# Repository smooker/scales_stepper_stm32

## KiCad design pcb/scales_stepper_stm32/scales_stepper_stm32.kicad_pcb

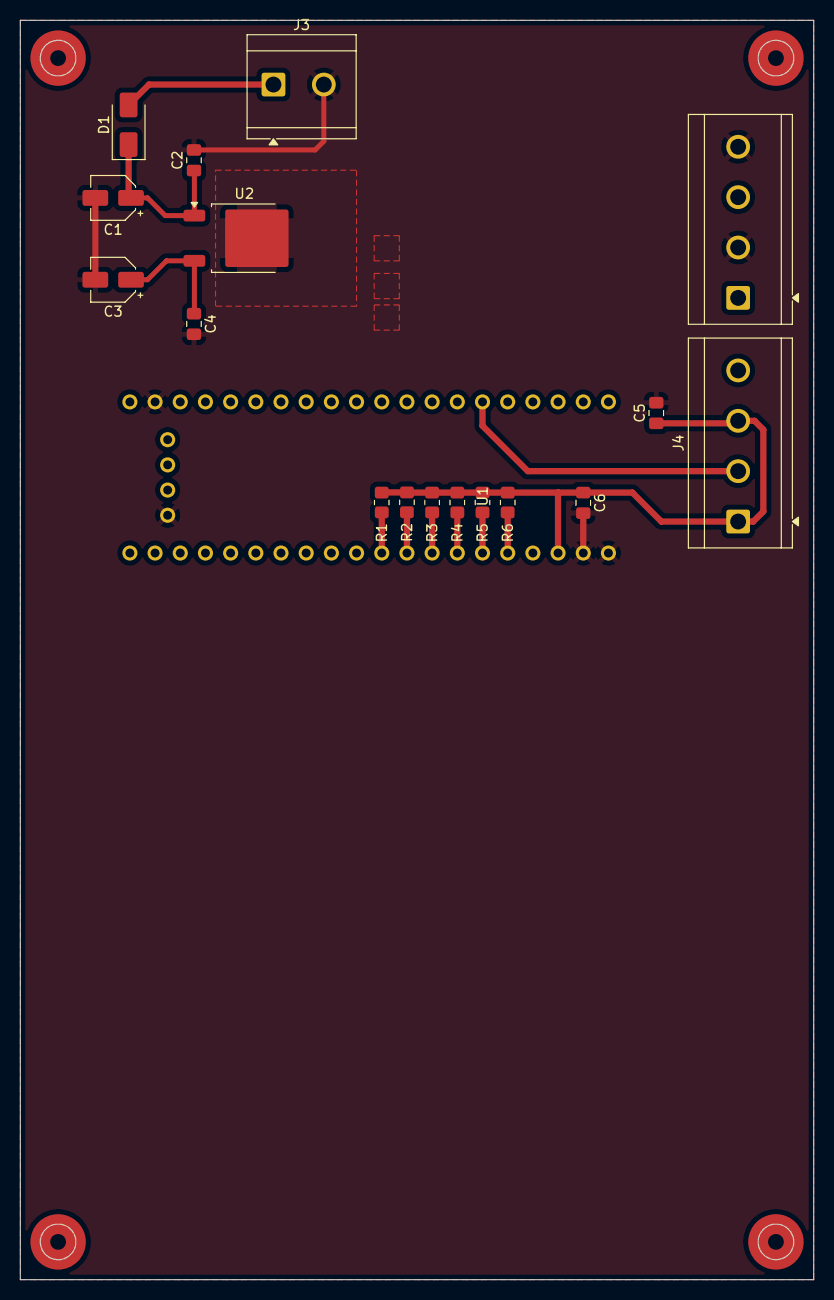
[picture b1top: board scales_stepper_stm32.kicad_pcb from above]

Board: 2 copper layers, 80.0 x 127.0 mm, 18 parts (0 on the bottom side), 13 nets.

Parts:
C1, C3: 47u; CP_Elec_4x4.5
C2, C4, C5, C6: 100n; C_0805_2012Metric_Pad1.18x1.45mm_HandSolder
D1: SS3200; D_SMA
J3: Screw_Terminal_01x02; TerminalBlock_CUI_TB007-508-02_1x02_P5.08mm_Horizontal
J4, J5: Screw_Terminal_01x04; TerminalBlock_CUI_TB007-508-04_1x04_P5.08mm_Horizontal
R1, R2, R3, R4, R5, R6: 1k; R_0805_2012Metric_Pad1.20x1.40mm_HandSolder
U1: BP; blue_pill
U2: LM78M05_TO252; TO-252-2

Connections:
+3V3: C5.1, C6.1, J4.1, J4.3, R1.1, R2.1, R3.1, R4.1, R5.1, R6.1, U1.3V3 (3.3V)
+5V: C3.1, C4.1, U2.3 (VO)
+24V: D1.2 (A), J3.1
BUTT_JOGL: R1.2, U1.PA6
BUTT_JOGR: R2.2, U1.PA7
BUTT_STEPL: R3.2, U1.PB0
BUTT_STEPR: R4.2, U1.PB1
DIR: J4.2, U1.PA9
ES_L: J5.1, R5.2, U1.PB10
ES_R: J5.3, R6.2, U1.PB11
GND: C1.2, C2.2, C3.2, C4.2, C5.2, C6.2, J3.2, J5.2, J5.4, U1.G (GND), U2.2 (GND)
unnamed: C1.1, C2.1, D1.1 (K), U2.1 (VI)
PULSE: J4.4, U1.PA8

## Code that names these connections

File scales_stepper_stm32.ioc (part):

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Mcu.Name=STM32F103C(8-B)Tx
Mcu.Package=LQFP48
Mcu.UserName=STM32F103C8Tx
PA11.Mode=Device
PA11.Signal=USB_DM
PA12.Mode=Device
PA12.Signal=USB_DP
PA13.Mode=Serial_Wire
PA13.Signal=SYS_JTMS-SWDIO
PA14.Mode=Serial_Wire
PA14.Signal=SYS_JTCK-SWCLK
PA6.GPIOParameters=GPIO_PuPd,GPIO_Label,GPIO_ModeDefaultEXTI
PA6.GPIO_Label=BUTT_JOGL
PA6.GPIO_ModeDefaultEXTI=GPIO_MODE_IT_RISING_FALLING
PA6.GPIO_PuPd=GPIO_PULLUP
PA6.Signal=GPXTI6
PA7.GPIOParameters=GPIO_PuPd,GPIO_Label,GPIO_ModeDefaultEXTI
PA7.GPIO_Label=BUTT_JOGR
PA7.GPIO_ModeDefaultEXTI=GPIO_MODE_IT_RISING_FALLING
PA7.GPIO_PuPd=GPIO_PULLUP
PA7.Signal=GPXTI7
PA8.GPIOParameters=PinState,GPIO_Label
PA8.GPIO_Label=PULSE
PA8.PinState=GPIO_PIN_SET
PA8.Signal=GPIO_Output
PA9.GPIOParameters=PinState,GPIO_Label
PA9.GPIO_Label=DIR
PA9.PinState=GPIO_PIN_SET
PA9.Signal=GPIO_Output
PB0.GPIOParameters=GPIO_PuPd,GPIO_Label,GPIO_ModeDefaultEXTI
PB0.GPIO_Label=BUTT_STEPL
PB0.GPIO_ModeDefaultEXTI=GPIO_MODE_IT_FALLING
PB0.GPIO_PuPd=GPIO_PULLUP
PB0.Signal=GPXTI0
PB1.GPIOParameters=GPIO_PuPd,GPIO_Label,GPIO_ModeDefaultEXTI
PB1.GPIO_Label=BUTT_STEPR
PB1.GPIO_ModeDefaultEXTI=GPIO_MODE_IT_FALLING
PB1.GPIO_PuPd=GPIO_PULLUP
PB1.Signal=GPXTI1
PB10.GPIOParameters=GPIO_PuPd,GPIO_Label,GPIO_ModeDefaultEXTI
PB10.GPIO_Label=ES_L
PB10.GPIO_ModeDefaultEXTI=GPIO_MODE_IT_RISING_FALLING
PB10.GPIO_PuPd=GPIO_PULLUP
PB10.Signal=GPXTI10
PB11.GPIOParameters=GPIO_PuPd,GPIO_Label,GPIO_ModeDefaultEXTI
PB11.GPIO_Label=ES_R
PB11.GPIO_ModeDefaultEXTI=GPIO_MODE_IT_RISING_FALLING
PB11.GPIO_PuPd=GPIO_PULLUP
PB11.Signal=GPXTI11
PB13.GPIOParameters=GPIO_PuPd,GPIO_Label
PB13.GPIO_Label=HX711_DATA
PB13.GPIO_PuPd=GPIO_PULLUP
PB13.Signal=GPIO_Input
PB14.GPIOParameters=GPIO_Label
PB14.GPIO_Label=HX711_CLK
PB14.Signal=GPIO_Output
PB15.GPIOParameters=PinState,GPIO_Label
PB15.GPIO_Label=BUZZ
PB15.PinState=GPIO_PIN_SET
PB15.Signal=GPIO_Output
PC13-TAMPER-RTC.GPIOParameters=GPIO_Label
PC13-TAMPER-RTC.GPIO_Label=LED_USER
PC13-TAMPER-RTC.Signal=GPIO_Output
PC14-OSC32_IN.Mode=LSE-External-Oscillator
PC14-OSC32_IN.Signal=RCC_OSC32_IN
PC15-OSC32_OUT.Mode=LSE-External-Oscillator
PC15-OSC32_OUT.Signal=RCC_OSC32_OUT
PD0-OSC_IN.Mode=HSE-External-Oscillator
PD0-OSC_IN.Signal=RCC_OSC_IN
PD1-OSC_OUT.Mode=HSE-External-Oscillator
PD1-OSC_OUT.Signal=RCC_OSC_OUT
RCC.SYSCLKFreq_VALUE=48000000
RCC.SYSCLKSource=RCC_SYSCLKSOURCE_PLLCLK
board=custom

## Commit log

2025-11-20 new file: scales_stepper_malinovski.ioc
2025-11-20 qtcreator files
2025-11-21 docs added
2025-12-02 mf.pl for generating. more important is usage of neshto.cflags
2025-12-09 USB OK. Parser to be done. Forced reenumeration before main
2025-12-09 Forgotten files. As a result - usb is not ok :)
2025-12-09 reverted to working state with stm32cubemx generated cdc
2025-12-28 udev rules working. the problem was ATTRS{interface}="intrerface name". Have to find a way to get teh name
2025-12-28 usb transmit fs status handling
2025-12-28 commands with strcmp. before parsing
2025-12-28 EEPROM emulation
2025-12-30 eeprom code to be in separate files
2025-12-30 AN2594 compatible EEPROM emulation code
2026-01-12 migrated to STM32F103C8T6
2026-01-12 regenerated and not needed files
2026-01-12 makefiles.sh added few folders
2026-01-12 ee added. eeprom emulation.
2026-01-12 submodule init
2026-01-13 help system. ongoing parsing of values for command input
2026-01-16 dumpio
2026-01-16 keyboard input and limit switches tested
2026-01-20 eeprom2 OK
2026-01-20 direction in go. Vmax during stage2 fixed.
2026-01-22 testing
2026-01-24 movement moved to main with semaphores bits
2026-01-24 as sym maloumen
2026-01-24 hybrid buttons... e.g. event and level based...
2026-01-24 steps has to be event based too. no missed event till now :)
2026-01-25 strong state machine
2026-01-28 BUG. gostep in interrupt routine instead in main
2026-02-05 final variables in eeprom
2026-02-07 movement with acc
2026-02-07 rising and falling on pb10 was wrong
2026-02-10 USB commands OK. not_cmplete flag was on the wrong place
2026-02-11 STEP works.
2026-02-12 TIM CNT = 0 in start
2026-02-14 fixed break from while in rampup and constvel on button release
2026-02-14 general code tidy. have to pass returned steps completed from jogrampup to constvel
2026-02-15 usb disconnection solved hUsbDeviceFS.dev_state != USBD_STATE_CONFIGURED
2026-02-15 pcb work
2026-02-16 morse code
2026-02-16 morse fixed with right timing
2026-02-16 morse ok
2026-02-23 float only for printf/vsprintf. sscanf had already
2026-02-24 general refactoring. getting rid of nanolibc printf and sscanf
2026-02-24 forgotten file
2026-02-25 str2float tested
2026-02-25 without float. 20kB less!
